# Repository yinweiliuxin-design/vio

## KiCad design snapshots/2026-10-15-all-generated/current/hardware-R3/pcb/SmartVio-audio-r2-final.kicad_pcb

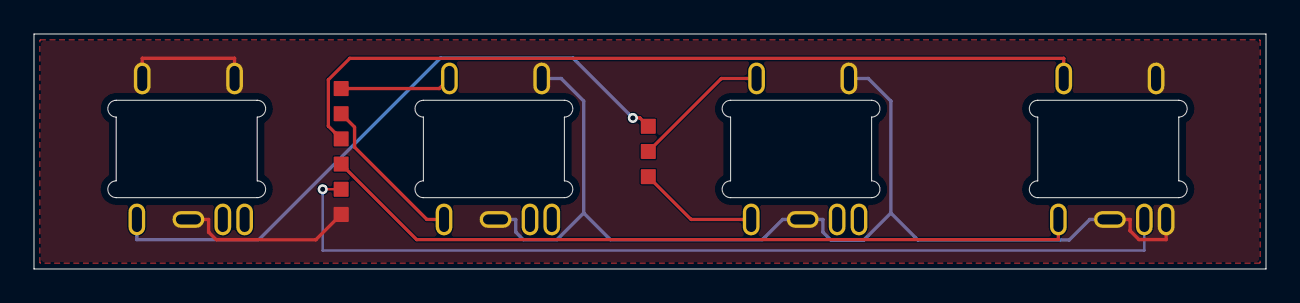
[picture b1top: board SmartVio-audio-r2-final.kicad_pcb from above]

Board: 2 copper layers, 73.4 x 14.0 mm, 6 parts (0 on the bottom side), 9 nets.

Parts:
H_AUDIO_1_R: PROPOSED_HARNESS_ENDPOINT; WirePads_6_P1.5
H_AUDIO_2_R: PROPOSED_HARNESS_ENDPOINT; WirePads_3_P1.5
J102, J201, J202, J301: STX-353K7A-6N-KTTR; Jack_Kycon_STX353K7A6N

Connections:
GND: H_AUDIO_1_R.1, J102.1 (SLEEVE), J102.2 (RING2_TRS_SLEEVE), J102.3 (RING1), J201.1 (SLEEVE), J201.2 (RING2_TRS_SLEEVE), J202.1 (SLEEVE), J202.2 (RING2_TRS_SLEEVE), J301.1 (SLEEVE), J301.2 (RING2_TRS_SLEEVE), J301.6 (DET_NO_B)
HP_DETECT_RAW: H_AUDIO_1_R.2, J301.5 (DET_NO_A)
HP_L_PORT: H_AUDIO_1_R.3, J301.4 (TIP)
HP_R_PORT: H_AUDIO_1_R.4, J301.3 (RING1)
LINE_L_PORT: H_AUDIO_1_R.5, J201.4 (TIP)
LINE_R_PORT: H_AUDIO_1_R.6, J201.3 (RING1)
RETURN_L_PORT: H_AUDIO_2_R.1, J202.4 (TIP)
RETURN_R_PORT: H_AUDIO_2_R.2, J202.3 (RING1)
SEND_T_PORT: H_AUDIO_2_R.3, J102.4 (TIP)

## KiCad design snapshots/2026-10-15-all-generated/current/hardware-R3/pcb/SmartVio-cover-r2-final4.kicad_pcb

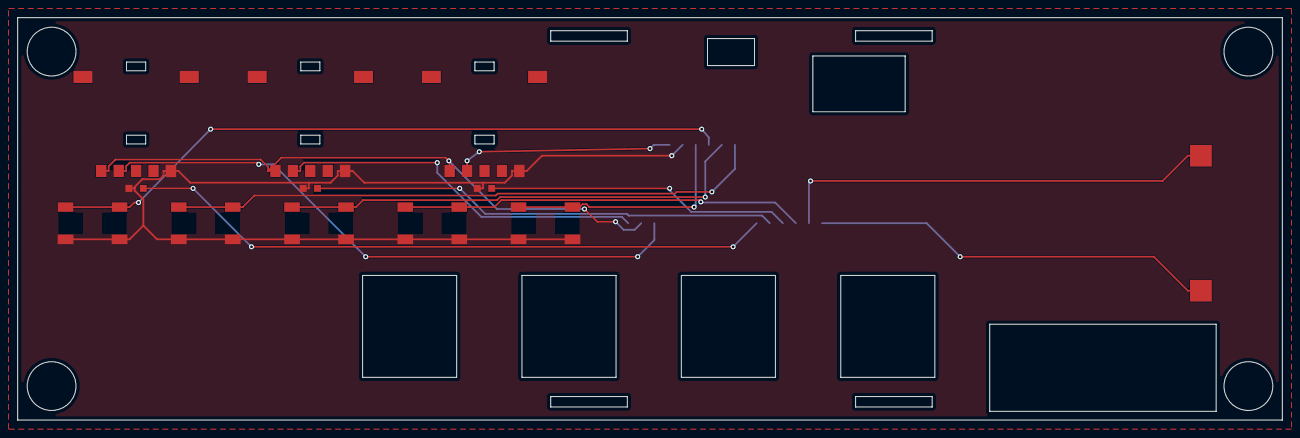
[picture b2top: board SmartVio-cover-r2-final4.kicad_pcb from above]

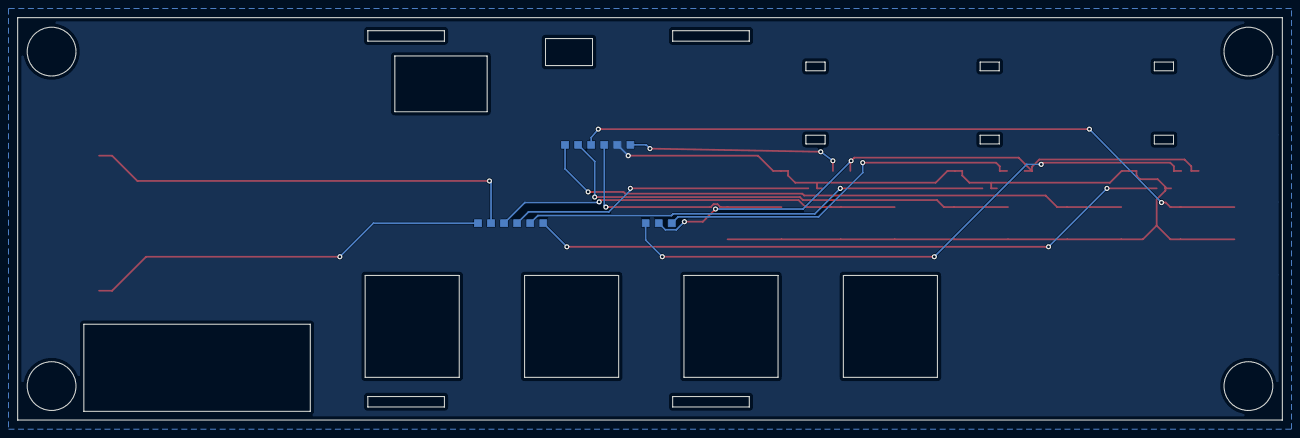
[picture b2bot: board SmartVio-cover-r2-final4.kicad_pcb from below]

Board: 2 copper layers, 145.2 x 46.2 mm, 15 parts (3 on the bottom side), 15 nets.

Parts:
D850, D851, D852: APT1608VRCXF/A-5MAV; LED_Kingbright_APT1608VRCXF_A_5MAV
H_COVER_1_R, H_COVER_2_R: PROPOSED_HARNESS_ENDPOINT; WirePads_6_P1.5
H_COVER_3_R: PROPOSED_HARNESS_ENDPOINT; WirePads_3_P1.5
LS901: AS01808AO-SC18-WP-R; Speaker_PUI_AS01808AO_SC18_Spring_REFERENCE
RV810, RV811, RV812: RK10J11R0A0L; Pot_Alps_RK10J11R0A0L
SW810, SW811, SW812, SW813, SW814: SKQGABE010; Switch_Alps_SKQGABE010

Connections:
FX_RAW: H_COVER_1_R.1, RV812.2 (WIPER)
GND: D850.1 (K), D851.1 (K), D852.1 (K), H_COVER_1_R.2, RV810.3 (LOW), RV811.3 (LOW), RV812.3 (LOW), SW810.3 (B1), SW810.4 (B2), SW811.3 (B1), SW811.4 (B2), SW812.3 (B1), SW812.4 (B2), SW813.3 (B1), SW813.4 (B2), SW814.3 (B1), SW814.4 (B2)
KEY_BT: H_COVER_1_R.3, SW814.1 (A1), SW814.2 (A2)
KEY_FX: H_COVER_1_R.4, SW810.1 (A1), SW810.2 (A2)
KEY_MIX: H_COVER_1_R.5, SW812.1 (A1), SW812.2 (A2)
KEY_MODE: H_COVER_1_R.6, SW811.1 (A1), SW811.2 (A2)
LED_ZONE_1_A: D850.2 (A), H_COVER_2_R.1
LED_ZONE_2_A: D851.2 (A), H_COVER_2_R.2
LED_ZONE_3_A: D852.2 (A), H_COVER_2_R.3
PWR_PB: H_COVER_2_R.4, SW813.1 (A1), SW813.2 (A2)
SPK_N: H_COVER_2_R.5, LS901.2 (-)
SPK_P: H_COVER_2_R.6, LS901.1 (+)
TONE_RAW: H_COVER_3_R.1, RV811.2 (WIPER)
V3D: H_COVER_3_R.2, RV810.1 (HIGH), RV811.1 (HIGH), RV812.1 (HIGH)
VOL_RAW: H_COVER_3_R.3, RV810.2 (WIPER)
